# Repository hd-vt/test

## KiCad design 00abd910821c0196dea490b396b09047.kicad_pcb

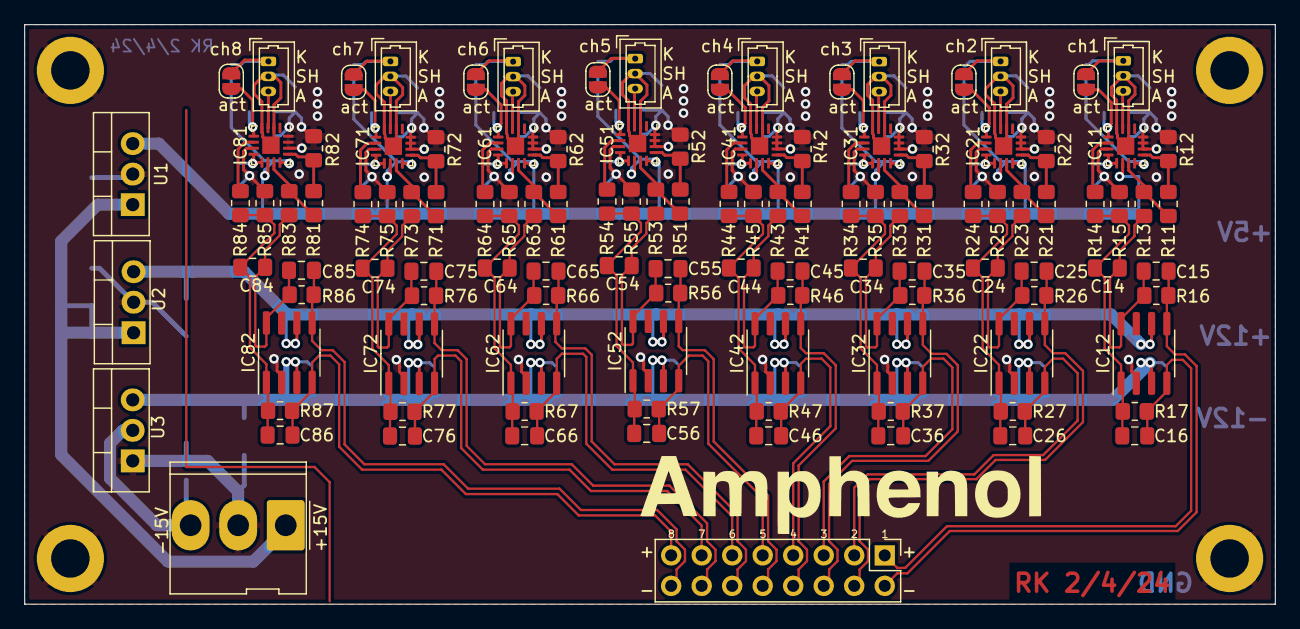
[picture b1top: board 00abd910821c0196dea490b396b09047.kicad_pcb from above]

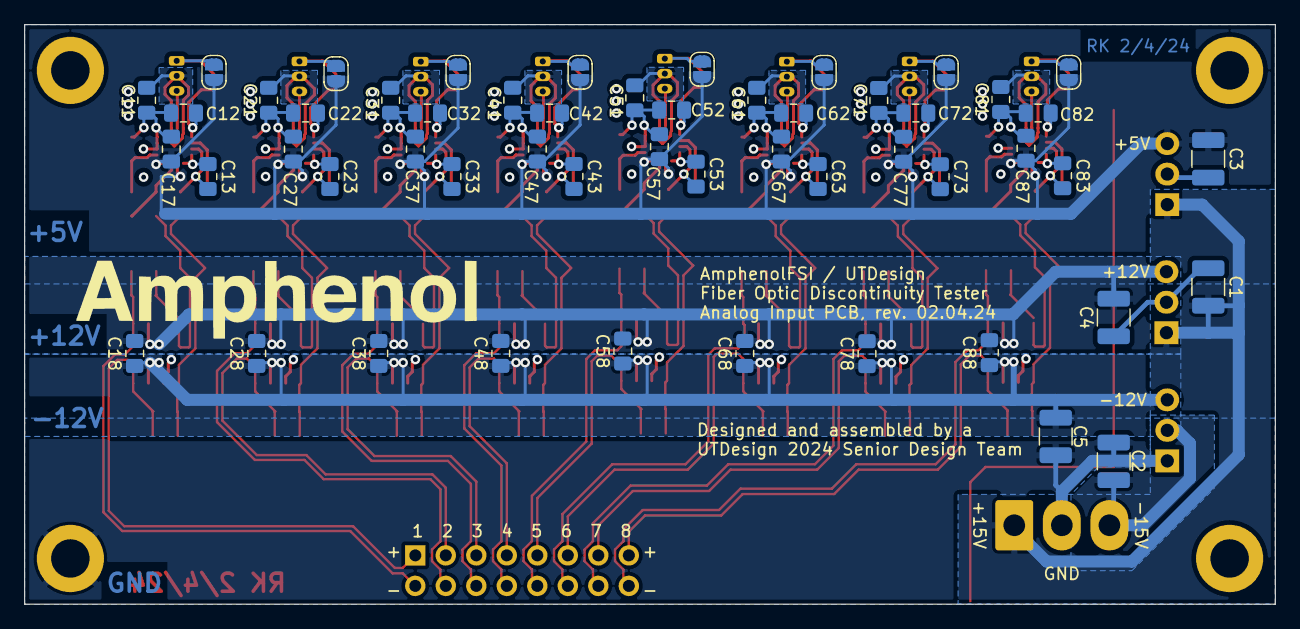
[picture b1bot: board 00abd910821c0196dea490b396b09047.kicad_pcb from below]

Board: 4 copper layers, 104.1 x 48.3 mm, 170 parts (53 on the bottom side), 102 nets.

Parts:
C1, C2, C3, C4, C5: 22u; C_1210_3225Metric_Pad1.33x2.70mm_HandSolder
C11, C12, C17, C18, C21, C22, C27, C28, C31, C32, C37, C38, C41, C42, C47, C48, C51, C52, C57, C58, C61, C62, C67, C68, C71, C72, C77, C78, C81, C82, C87, C88: 100n; C_0805_2012Metric_Pad1.18x1.45mm_HandSolder
C13, C23, C33, C43, C53, C63, C73, C83: 18p; C_0805_2012Metric_Pad1.18x1.45mm_HandSolder
C14, C24, C34, C44, C54, C64, C74, C84: 220p; C_0805_2012Metric_Pad1.18x1.45mm_HandSolder
C15, C16, C25, C26, C35, C36, C45, C46, C55, C56, C65, C66, C75, C76, C85, C86: 2.2p; C_0805_2012Metric_Pad1.18x1.45mm_HandSolder
IC11, IC21, IC31, IC41, IC51, IC61, IC71, IC81: ADL5303ACPZ-R7; QFN-16-1EP_3x3mm_P0.5mm_EP1.45x1.45mm
IC12, IC22, IC32, IC42, IC52, IC62, IC72, IC82: THS4141CD; SOIC-8_3.9x4.9mm_P1.27mm
J1, J2, J3, J4, J5, J6, J7, J8: Conn_01x03_Female; Molex_PicoBlade_53047-0310_1x03_P1.25mm_Vertical
J9: Conn_02x08_Odd_Even; PinHeader_2x08_P2.54mm_Vertical
J10: Conn_01x03_Female; Molex_KK-396_5273-03A_1x03_P3.96mm_Vertical
JP11, JP12, JP21, JP22, JP31, JP32, JP41, JP42, JP51, JP52, JP61, JP62, JP71, JP72, JP81, JP82: SolderJumper_2_Open; SolderJumper-2_P1.3mm_Open_RoundedPad1.0x1.5mm
R11, R12, R21, R22, R31, R32, R41, R42, R51, R52, R61, R62, R71, R72, R81, R82: 10k; R_0805_2012Metric_Pad1.20x1.40mm_HandSolder
R13, R23, R33, R43, R53, R63, R73, R83: 6.8k; R_0805_2012Metric_Pad1.20x1.40mm_HandSolder
R14, R24, R34, R44, R54, R64, R74, R84: 8.2k; R_0805_2012Metric_Pad1.20x1.40mm_HandSolder
R15, R25, R35, R45, R55, R65, R75, R85: 33k; R_0805_2012Metric_Pad1.20x1.40mm_HandSolder
R16, R17, R26, R27, R36, R37, R46, R47, R56, R57, R66, R67, R76, R77, R86, R87: 54.9k; R_0805_2012Metric_Pad1.20x1.40mm_HandSolder
U1: LM7805_TO220; TO-220-3_Vertical
U2: LM7812_TO220; TO-220-3_Vertical
U3: MC79M12_TO220; TO-220-3_Vertical

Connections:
+5V: C3.1, C17.2, C27.2, C37.2, C47.2, C57.2, C67.2, C77.2, C87.2, IC11.10 (VPS2), IC11.12 (VPS1), IC21.10 (VPS2), IC21.12 (VPS1), IC31.10 (VPS2), IC31.12 (VPS1), IC41.10 (VPS2), IC41.12 (VPS1), IC51.10 (VPS2), IC51.12 (VPS1), IC61.10 (VPS2), IC61.12 (VPS1), IC71.10 (VPS2), IC71.12 (VPS1), IC81.10 (VPS2), IC81.12 (VPS1), JP11.2 (B), JP21.2 (B), JP31.2 (B), JP41.2 (B), JP51.2 (B), JP61.2 (B), JP71.2 (B), JP81.2 (B), U1.3 (VO)
+12V: C4.1, C18.2, C28.2, C38.2, C48.2, C58.2, C68.2, C78.2, C88.2, IC12.6 (VCC-), IC22.6 (VCC-), IC32.6 (VCC-), IC42.6 (VCC-), IC52.6 (VCC-), IC62.6 (VCC-), IC72.6 (VCC-), IC82.6 (VCC-), U2.3 (VO)
+15V: C1.1, J10.1, U1.1 (VI), U2.1 (VI)
-12V: C5.2, C18.1, C28.1, C38.1, C48.1, C58.1, C68.1, C78.1, C88.1, IC12.3 (VCC+), IC22.3 (VCC+), IC32.3 (VCC+), IC42.3 (VCC+), IC52.3 (VCC+), IC62.3 (VCC+), IC72.3 (VCC+), IC82.3 (VCC+), U3.3 (VO)
-15V: C2.2, J10.3, U3.2 (VI)
/TIA1/BF_NG: IC11.13 (BFNG), R11.2, R12.2
/TIA1/BF_OUT: IC11.11 (VOUT), R11.1, R13.1
/TIA1/PD_A: IC11.3 (INPT), J1.3
/TIA1/PD_K: J1.1, JP11.1 (A), JP12.1 (A)
/TIA1/STAGE_2_IN+: C14.2, C15.2, IC12.8 (VIN+), R13.2, R16.2
/TIA1/STAGE_2_IN-: C14.1, C16.1, IC12.1 (VIN-), R14.2, R15.1, R17.1
/TIA1/VLOG: C13.1, IC11.8 (VLOG), IC11.9 (BFIN)
/TIA1/VPDB: C12.1, IC11.5 (VPDB), JP12.2 (B)
/TIA1/VREF: IC11.6 (VREF), R14.1
/TIA1/VSUM: C11.1, IC11.2 (VSUM_1), IC11.4 (VSUM_2), IC11.17 (EP), J1.2
/TIA2/BF_NG: IC21.13 (BFNG), R21.2, R22.2
/TIA2/BF_OUT: IC21.11 (VOUT), R21.1, R23.1
/TIA2/PD_A: IC21.3 (INPT), J2.3
/TIA2/PD_K: J2.1, JP21.1 (A), JP22.1 (A)
/TIA2/STAGE_2_IN+: C24.2, C25.2, IC22.8 (VIN+), R23.2, R26.2
/TIA2/STAGE_2_IN-: C24.1, C26.1, IC22.1 (VIN-), R24.2, R25.1, R27.1
/TIA2/VLOG: C23.1, IC21.8 (VLOG), IC21.9 (BFIN)
/TIA2/VPDB: C22.1, IC21.5 (VPDB), JP22.2 (B)
/TIA2/VREF: IC21.6 (VREF), R24.1
/TIA2/VSUM: C21.1, IC21.2 (VSUM_1), IC21.4 (VSUM_2), IC21.17 (EP), J2.2
/TIA3/BF_NG: IC31.13 (BFNG), R31.2, R32.2
/TIA3/BF_OUT: IC31.11 (VOUT), R31.1, R33.1
/TIA3/PD_A: IC31.3 (INPT), J3.3
/TIA3/PD_K: J3.1, JP31.1 (A), JP32.1 (A)
/TIA3/STAGE_2_IN+: C34.2, C35.2, IC32.8 (VIN+), R33.2, R36.2
/TIA3/STAGE_2_IN-: C34.1, C36.1, IC32.1 (VIN-), R34.2, R35.1, R37.1
/TIA3/VLOG: C33.1, IC31.8 (VLOG), IC31.9 (BFIN)
/TIA3/VPDB: C32.1, IC31.5 (VPDB), JP32.2 (B)
/TIA3/VREF: IC31.6 (VREF), R34.1
/TIA3/VSUM: C31.1, IC31.2 (VSUM_1), IC31.4 (VSUM_2), IC31.17 (EP), J3.2
/TIA4/BF_NG: IC41.13 (BFNG), R41.2, R42.2
/TIA4/BF_OUT: IC41.11 (VOUT), R41.1, R43.1
/TIA4/PD_A: IC41.3 (INPT), J4.3
/TIA4/PD_K: J4.1, JP41.1 (A), JP42.1 (A)
/TIA4/STAGE_2_IN+: C44.2, C45.2, IC42.8 (VIN+), R43.2, R46.2
/TIA4/STAGE_2_IN-: C44.1, C46.1, IC42.1 (VIN-), R44.2, R45.1, R47.1
/TIA4/VLOG: C43.1, IC41.8 (VLOG), IC41.9 (BFIN)
/TIA4/VPDB: C42.1, IC41.5 (VPDB), JP42.2 (B)
/TIA4/VREF: IC41.6 (VREF), R44.1
/TIA4/VSUM: C41.1, IC41.2 (VSUM_1), IC41.4 (VSUM_2), IC41.17 (EP), J4.2
/TIA5/BF_NG: IC51.13 (BFNG), R51.2, R52.2
/TIA5/BF_OUT: IC51.11 (VOUT), R51.1, R53.1
/TIA5/PD_A: IC51.3 (INPT), J5.3
/TIA5/PD_K: J5.1, JP51.1 (A), JP52.1 (A)
/TIA5/STAGE_2_IN+: C54.2, C55.2, IC52.8 (VIN+), R53.2, R56.2
/TIA5/STAGE_2_IN-: C54.1, C56.1, IC52.1 (VIN-), R54.2, R55.1, R57.1
/TIA5/VLOG: C53.1, IC51.8 (VLOG), IC51.9 (BFIN)
/TIA5/VPDB: C52.1, IC51.5 (VPDB), JP52.2 (B)
/TIA5/VREF: IC51.6 (VREF), R54.1
/TIA5/VSUM: C51.1, IC51.2 (VSUM_1), IC51.4 (VSUM_2), IC51.17 (EP), J5.2
/TIA6/BF_NG: IC61.13 (BFNG), R61.2, R62.2
/TIA6/BF_OUT: IC61.11 (VOUT), R61.1, R63.1
/TIA6/PD_A: IC61.3 (INPT), J6.3
/TIA6/PD_K: J6.1, JP61.1 (A), JP62.1 (A)
/TIA6/STAGE_2_IN+: C64.2, C65.2, IC62.8 (VIN+), R63.2, R66.2
/TIA6/STAGE_2_IN-: C64.1, C66.1, IC62.1 (VIN-), R64.2, R65.1, R67.1
/TIA6/VLOG: C63.1, IC61.8 (VLOG), IC61.9 (BFIN)
/TIA6/VPDB: C62.1, IC61.5 (VPDB), JP62.2 (B)
/TIA6/VREF: IC61.6 (VREF), R64.1
/TIA6/VSUM: C61.1, IC61.2 (VSUM_1), IC61.4 (VSUM_2), IC61.17 (EP), J6.2
/TIA7/BF_NG: IC71.13 (BFNG), R71.2, R72.2
/TIA7/BF_OUT: IC71.11 (VOUT), R71.1, R73.1
/TIA7/PD_A: IC71.3 (INPT), J7.3
/TIA7/PD_K: J7.1, JP71.1 (A), JP72.1 (A)
/TIA7/STAGE_2_IN+: C74.2, C75.2, IC72.8 (VIN+), R73.2, R76.2
/TIA7/STAGE_2_IN-: C74.1, C76.1, IC72.1 (VIN-), R74.2, R75.1, R77.1
/TIA7/VLOG: C73.1, IC71.8 (VLOG), IC71.9 (BFIN)
/TIA7/VPDB: C72.1, IC71.5 (VPDB), JP72.2 (B)
/TIA7/VREF: IC71.6 (VREF), R74.1
/TIA7/VSUM: C71.1, IC71.2 (VSUM_1), IC71.4 (VSUM_2), IC71.17 (EP), J7.2
/TIA8/BF_NG: IC81.13 (BFNG), R81.2, R82.2
/TIA8/BF_OUT: IC81.11 (VOUT), R81.1, R83.1
/TIA8/PD_A: IC81.3 (INPT), J8.3
/TIA8/PD_K: J8.1, JP81.1 (A), JP82.1 (A)
/TIA8/STAGE_2_IN+: C84.2, C85.2, IC82.8 (VIN+), R83.2, R86.2
/TIA8/STAGE_2_IN-: C84.1, C86.1, IC82.1 (VIN-), R84.2, R85.1, R87.1
/TIA8/VLOG: C83.1, IC81.8 (VLOG), IC81.9 (BFIN)
/TIA8/VPDB: C82.1, IC81.5 (VPDB), JP82.2 (B)
/TIA8/VREF: IC81.6 (VREF), R84.1
/TIA8/VSUM: C81.1, IC81.2 (VSUM_1), IC81.4 (VSUM_2), IC81.17 (EP), J8.2
CH1+: C16.2, IC12.4 (VOUT+), J9.1, R17.2
CH1-: C15.1, IC12.5 (VOUT-), J9.2, R16.1
CH2+: C26.2, IC22.4 (VOUT+), J9.3, R27.2
CH2-: C25.1, IC22.5 (VOUT-), J9.4, R26.1
CH3+: C36.2, IC32.4 (VOUT+), J9.5, R37.2
CH3-: C35.1, IC32.5 (VOUT-), J9.6, R36.1
CH4+: C46.2, IC42.4 (VOUT+), J9.7, R47.2
CH4-: C45.1, IC42.5 (VOUT-), J9.8, R46.1
CH5+: C56.2, IC52.4 (VOUT+), J9.9, R57.2
CH5-: C55.1, IC52.5 (VOUT-), J9.10, R56.1
CH6+: C66.2, IC62.4 (VOUT+), J9.11, R67.2
CH6-: C65.1, IC62.5 (VOUT-), J9.12, R66.1
CH7+: C76.2, IC72.4 (VOUT+), J9.13, R77.2
CH7-: C75.1, IC72.5 (VOUT-), J9.14, R76.1
CH8+: C86.2, IC82.4 (VOUT+), J9.15, R87.2
CH8-: C85.1, IC82.5 (VOUT-), J9.16, R86.1
GND: C1.2, C2.1, C3.2, C4.2, C5.1, C11.2, C12.2, C13.2, C17.1, C21.2, C22.2, C23.2, C27.1, C31.2, C32.2, C33.2, C37.1, C41.2, C42.2, C43.2, C47.1, C51.2, C52.2, C53.2, C57.1, C61.2, C62.2, C63.2, C67.1, C71.2, C72.2, C73.2, C77.1, C81.2, C82.2, C83.2, C87.1, IC11.7 (ACOM), IC11.14 (GND_1), IC11.15 (GND_2), IC11.16 (PWDN), IC12.2 (VOCM), IC21.7 (ACOM), IC21.14 (GND_1), IC21.15 (GND_2), IC21.16 (PWDN), IC22.2 (VOCM), IC31.7 (ACOM), IC31.14 (GND_1), IC31.15 (GND_2), IC31.16 (PWDN), IC32.2 (VOCM), IC41.7 (ACOM), IC41.14 (GND_1), IC41.15 (GND_2), IC41.16 (PWDN), IC42.2 (VOCM), IC51.7 (ACOM), IC51.14 (GND_1), IC51.15 (GND_2), IC51.16 (PWDN), IC52.2 (VOCM), IC61.7 (ACOM), IC61.14 (GND_1), IC61.15 (GND_2), IC61.16 (PWDN), IC62.2 (VOCM), IC71.7 (ACOM), IC71.14 (GND_1), IC71.15 (GND_2), IC71.16 (PWDN), IC72.2 (VOCM), IC81.7 (ACOM), IC81.14 (GND_1), IC81.15 (GND_2), IC81.16 (PWDN), IC82.2 (VOCM), J10.2, R12.1, R15.2, R22.1, R25.2, R32.1, R35.2, R42.1, R45.2, R52.1, R55.2, R62.1, R65.2, R72.1, R75.2, R82.1, R85.2, U1.2 (GND), U2.2 (GND), U3.1 (GND)
